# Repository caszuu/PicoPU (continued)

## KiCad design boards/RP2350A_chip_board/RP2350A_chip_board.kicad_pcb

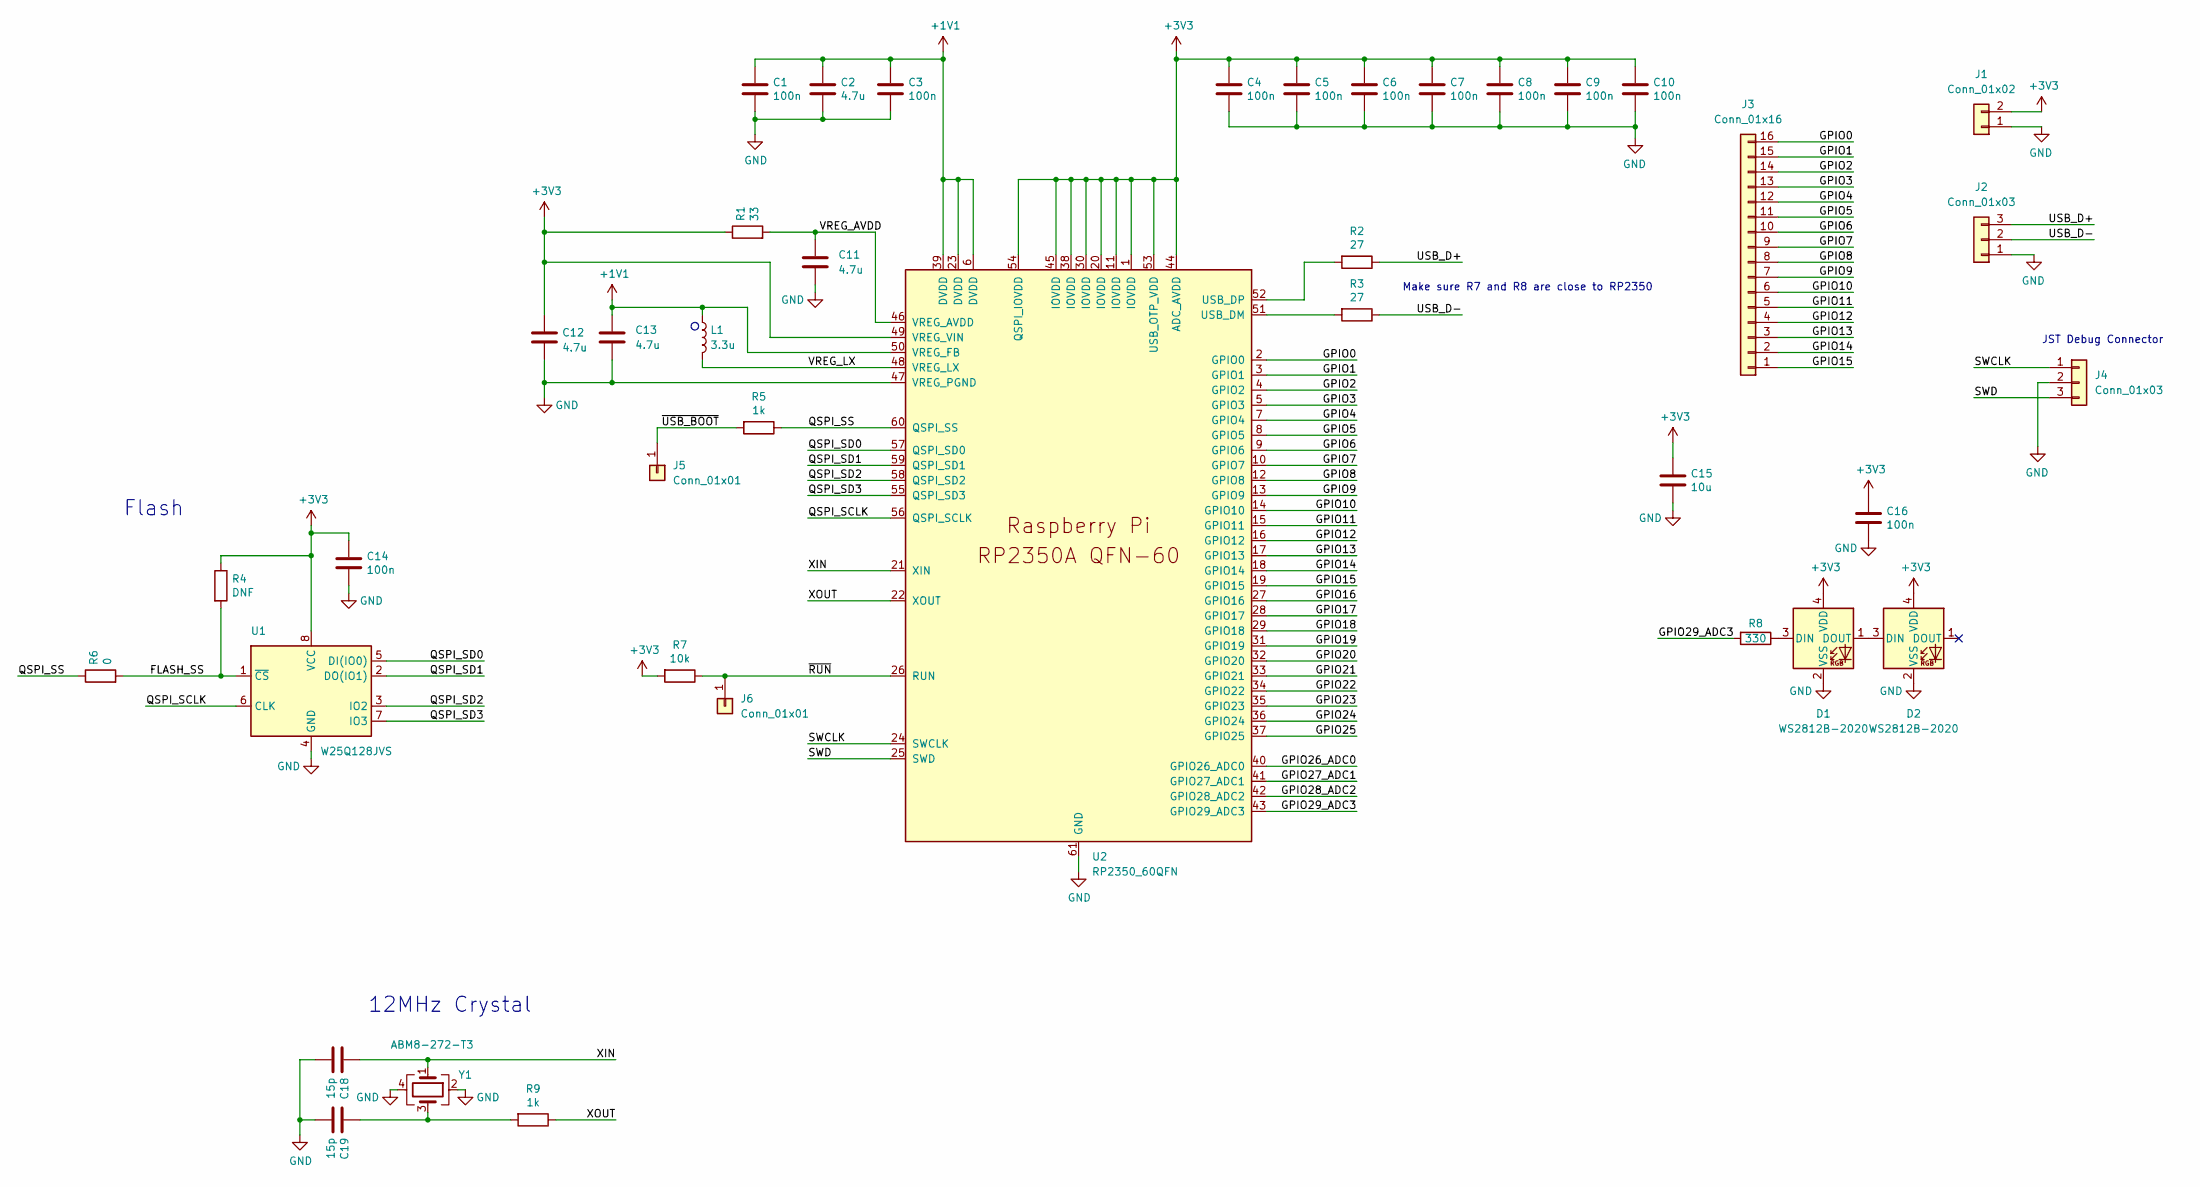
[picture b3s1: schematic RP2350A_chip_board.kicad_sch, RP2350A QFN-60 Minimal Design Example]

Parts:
C1, C3, C4, C5, C6, C7, C8, C9, C10, C14, C16: 100n; C_0402_1005Metric
C2, C11: 4.7u; C_0402_1005Metric
C12, C13: 4.7u; C_0402_1005Metric_small_pads
C15: 10u; C_0805_2012Metric
C18, C19: 15p; C_0402_1005Metric
D1, D2: WS2812B-2020; LED_WS2812B-2020_PLCC4_2.0x2.0mm
J1: Conn_01x02; PinSocket_1x02_P2.00mm_Vertical
J2, J4: Conn_01x03; PinSocket_1x03_P2.54mm_Vertical
J3: Conn_01x16; PinSocket_1x16_P2.00mm_Vertical
J5, J6: Conn_01x01; PinSocket_1x01_P2.54mm_Vertical
L1: 3.3u; L_pol_2016
R1: 33; R_0402_1005Metric
R2, R3: 27; R_0402_1005Metric
R4: DNF; R_0402_1005Metric
R5, R9: 1k; R_0402_1005Metric
R6: 0; R_0402_1005Metric
R7: 10k; R_0402_1005Metric
R8: 330; R_0402_1005Metric
U1: W25Q128JVS; SOIC-8_5.23x5.23mm_P1.27mm
U2: RP2350_60QFN; RP2350-QFN-60-1EP_7x7_P0.4mm_EP3.4x3.4mm_ThermalVias
Y1: ABM8-272-T3; Crystal_SMD_3225-4Pin_3.2x2.5mm

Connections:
+1V1: C1.1, C2.1, C3.1, C13.1, L1.1, U2.6 (DVDD), U2.23 (DVDD), U2.39 (DVDD), U2.50 (VREG_FB)
+3V3: C4.1, C5.1, C6.1, C7.1, C8.1, C9.1, C10.1, C12.1, C14.1, C15.1, C16.1, D1.4 (VDD), D2.4 (VDD), J1.2, R1.1, R4.1, R7.2, U1.8 (VCC), U2.1 (IOVDD), U2.11 (IOVDD), U2.20 (IOVDD), U2.30 (IOVDD), U2.38 (IOVDD), U2.44 (ADC_AVDD), U2.45 (IOVDD), U2.49 (VREG_VIN), U2.53 (USB_OTP_VDD), U2.54 (QSPI_IOVDD); also elsewhere on the board
/FLASH_SS: R4.2, R6.2, U1.1 (~CS)
/GPIO0: J3.16, U2.2 (GPIO0)
/GPIO1: J3.15, U2.3 (GPIO1)
/GPIO2: J3.14, U2.4 (GPIO2)
/GPIO3: J3.13, U2.5 (GPIO3)
/GPIO4: J3.12, U2.7 (GPIO4)
/GPIO5: J3.11, U2.8 (GPIO5)
/GPIO6: J3.10, U2.9 (GPIO6)
/GPIO7: J3.9, U2.10 (GPIO7)
/GPIO8: J3.8, U2.12 (GPIO8)
/GPIO9: J3.7, U2.13 (GPIO9)
/GPIO10: J3.6, U2.14 (GPIO10)
/GPIO11: J3.5, U2.15 (GPIO11)
/GPIO12: J3.4, U2.16 (GPIO12)
/GPIO13: J3.3, U2.17 (GPIO13)
/GPIO14: J3.2, U2.18 (GPIO14)
/GPIO15: J3.1, U2.19 (GPIO15)
/GPIO16: U2.27 (GPIO16)
/GPIO17: U2.28 (GPIO17)
/GPIO18: U2.29 (GPIO18)
/GPIO19: U2.31 (GPIO19)
/GPIO20: U2.32 (GPIO20)
/GPIO21: U2.33 (GPIO21)
/GPIO22: U2.34 (GPIO22)
/GPIO23: U2.35 (GPIO23)
/GPIO24: U2.36 (GPIO24)
/GPIO25: U2.37 (GPIO25)
/GPIO26_ADC0: U2.40 (GPIO26_ADC0)
/GPIO27_ADC1: U2.41 (GPIO27_ADC1)
/GPIO28_ADC2: U2.42 (GPIO28_ADC2)
/GPIO29_ADC3: R8.2, U2.43 (GPIO29_ADC3)
/QSPI_SCLK: U1.6 (CLK), U2.56 (QSPI_SCLK)
/QSPI_SD0: U1.5 (DI(IO0)), U2.57 (QSPI_SD0)
/QSPI_SD1: U1.2 (DO(IO1)), U2.59 (QSPI_SD1)
/QSPI_SD2: U1.3 (IO2), U2.58 (QSPI_SD2)
/QSPI_SD3: U1.7 (IO3), U2.55 (QSPI_SD3)
/QSPI_SS: R5.1, R6.1, U2.60 (QSPI_SS)
/SWCLK: J4.1, U2.24 (SWCLK)
/SWD: J4.3, U2.25 (SWD)
/USB_D+: J2.3, R2.1
/USB_D-: J2.2, R3.1
/VREG_AVDD: C11.1, R1.2, U2.46 (VREG_AVDD)
/VREG_LX: L1.2, U2.48 (VREG_LX)
/XIN: C18.1, U2.21 (XIN), Y1.1
/XOUT: R9.1, U2.22 (XOUT)
/~RUN: J6.1, R7.1, U2.26 (RUN)
/~USB_BOOT: J5.1, R5.2
GND: C1.2, C2.2, C3.2, C4.2, C5.2, C6.2, C7.2, C8.2, C9.2, C10.2, C11.2, C12.2, C13.2, C14.2, C15.2, C16.2, C18.2, C19.2, D1.2 (VSS), D2.2 (VSS), J1.1, J2.1, J4.2, U1.4 (GND), U2.47 (VREG_PGND), U2.61 (GND), Y1.2, Y1.4; also elsewhere on the board
unnamed: C19.1, R9.2, Y1.3
unnamed: D1.3 (DIN), R8.1
unnamed: D1.1 (DOUT), D2.3 (DIN)
unnamed: R3.2, U2.51 (USB_DM)
unnamed: R2.2, U2.52 (USB_DP)

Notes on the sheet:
JST Debug Connector
Flash
Make sure R7 and R8 are close to RP2350
12MHz Crystal

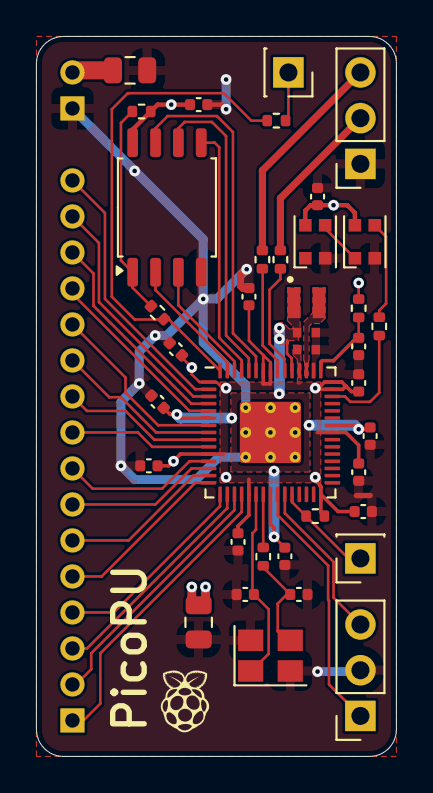
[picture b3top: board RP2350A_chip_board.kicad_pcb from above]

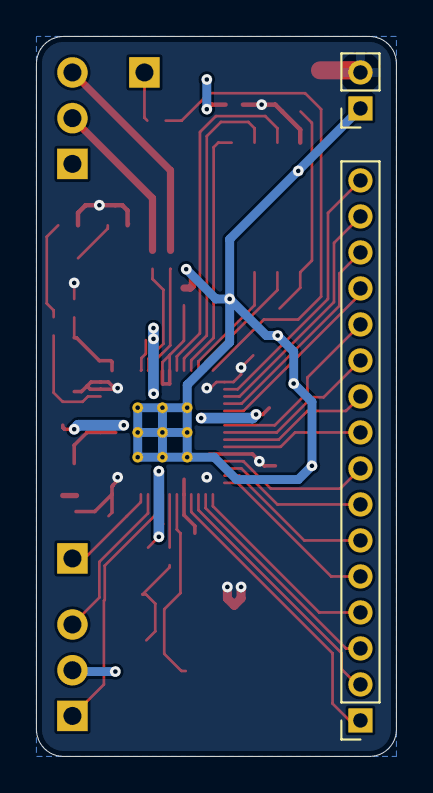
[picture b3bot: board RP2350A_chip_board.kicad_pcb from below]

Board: 2 copper layers, 20.0 x 40.0 mm, 40 parts (2 on the bottom side), 42 nets.

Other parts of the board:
C5#2: 100n; C_0402_1005Metric

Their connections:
+3V3: C5#2.1; also elsewhere on the board
GND: C5#2.2; also elsewhere on the board

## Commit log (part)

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2024-08-16 add dbg gcs packet and fixup vertex stage and control logic
2024-08-17 implemented simd rasterizer and fragment stage + cleanup
2024-08-17 add README files and credit
2024-08-17 added license
2024-08-17 add board designs
2024-08-18 Add Broker board
2024-08-19 mostly fixed up rasterizer and fragment stage
2024-08-19 rewrote rasterizer implementation
    the original rasterizer was mostly a direct
    rewrite of the ryn's simd sw rasterizer which
    poorly mapped to the m33 chip. this impl while
    much slower is mostly correct, unlike the last
2024-08-20 improved rasterizer w testing
2024-08-20 fixed broker-sim serial + fragment stage cleanup
2024-08-28 cleanup firmware dir
2024-08-28 firmware: added a clang-format file + cleanup
2024-08-28 firmware: work on expanding the GCS pipeline
    - added proper vertex shader and
    post-processing stages
    - implemented w_tile offsets in rasterizer
2024-12-28 *very* WIP uber commit
    - added device-side usbd driver
    - initial host-side pyhost python driver
    - replace ex_simd with gcc vector types
2025-01-31 firmware: added SCS + work on usbd
2025-01-31 firmware: rewrote raster stage implementation
2025-04-07 shader: more raster-stage and GCS work
    - added async tile request support to raster
    - added "v2f" state bewteen gcs stages
    - added dma_mem helper funcs
    - changed GCS to a more batch based approach
2025-05-24 shader: added dvid and si_proto (+ WIP)
    Apart from the dvi and si implementation, this
    uber commit carries of a lot on WIP and temporary
    code of questionable quality. It's here just for
    backup reasons before moving away from the single
    chip arch to the to-be-commited `pdrv` driver and
    proper multi chip firmware.
2025-05-24 pdrv: initial commit
2025-06-13 shader: remove multi-arch shader fw
2025-06-13 usbd: replace old hb driver with a rewrite
    this replaces the old hostbus driver used with
    pyhost with a new impl developed in parallel with
    pdrv and its usb protocol.
    also the driver needed a rewrite in general now
    that i know how tinyusb works.
2025-06-23 dvid: add support for arbitrary modeset profiles
2025-06-23 usbd: add support for stream xfers
2025-06-23 gcs: add support for basic vram over `chip.h`
2025-06-23 mockbird: add initial firmware
    this commit is a heavy modification / rewrite of
    the `shader_core` binary. unlike it, it features
    a broker-like fw layer and supports initial
    versions of pdrv cmdbufs, ucmds and control paks
2025-06-23 pdrv: add early support for cmdbufs, scmds and vram
    pdrv can now submit memory transfers and dispatch
    very simple command buffers. most is exposed using
    a vulkan-like api and can be driven by external code.
    see `bench/` for a very minimal example.
2025-06-23 pdrv: update bench with new pdrv features
2025-06-23 docs: update readme
2025-06-23 pdrv: remove legacy si protocol
2025-06-30 boards: upload new EasyEDA files, instead of old KiCad files
2025-07-30 pdrv: add basic sync and vram utilities
    - added `Fence` for basic device sync
    - added `Staging` for device usable host buffers
    - added a tiny vram heap allocator
2025-07-30 pdrv: add background readback goroutines
2025-07-30 pdrv: finish `mock` arch encoders and support
2025-07-30 pdrv: update bench with new pdrv changes
2025-09-04 chore: add missing `pico_sdk_import.cmake` module
    I'm surprised that i didn't notice this earlier,
    the project should now build from a clean clone.
2025-09-04 gcs: refactor rasterizer and overall clean up
    The rough tile rasterizer loop was replaced in
    favor of sorted bounding box edge lists. This
    greatly improves perf in cases where primitives
    don't cover large portions of the rasterized area
    by skipping tiles which are not covered by their
    bboxes.
2025-10-15 fw: add multicore helper
2025-10-15 gcs: add point rasterizer + dual-core raster stage
    only the rasterizer stage is parallel so far. the
    vertex stage is left synchronous for now as extra
    care has to be taken to perserve api order when
    submitting clips to the raster stage.
2025-10-15 dvid: add support for integer scaling
2026-01-19 fw/chore: rework file structure (for the last time)
    This repo ended up with a lot of tech debt and dead
    code. Hopefully this should be the last purge, while
    moving towards a new mesa driver implementation.
2026-02-10 util: add `u_fifo` (generic ring buffer)
2026-02-10 pl: initial pico-link driver
    the current driver implementation is *very* work
    in progress and only being commited as a backup.
    it is not prod ready yet.
2026-02-10 usbd: add a `hwq` interface driver
    this interface is primarily used for work submition
    from the host that is synchronized and scheduled by
    the device. (unlike dev_ctl)
2026-03-08 pl: general fixes to the driver
2026-03-10 pl: add optional perf monitoring
    Allow the user to optionally compile in a few
    basic performance counters primarily for sustained
    workload debugging.
2026-03-10 chore: clean up outdated files
2026-04-04 cp: initial cmd processor implementation
2026-04-04 usbd: modify `hwq` for the new cmd processor
